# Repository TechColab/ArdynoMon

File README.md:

# ArdynoMon
Arduino shield for DIY dynos, engine monitoring &amp; more.  
Designed for monitoring & logging key aspects of an internal combustion engine for the purpose of R&D for my own Engine Management system. 
Aims to be the natural successor for the "Ardyno" shield https://ardyno.weebly.com/ with more input options & logging.  

Basically, it uses the Arduino's two interrupts to accuately record one or two channels of engine cycle events.  
While the original Ardyno would use one signal from an inertia drum roller & one signal from the ignition system, this ArdynoMon can alternatively be used to get both signals from different parts of the ignition system.  

# 2026-02-14 Revision 3.6 addresses all know issues.
    After some external interest (thank you) I've been nudged into refreshing this page.  
	I still get a bit lost with KiCAD files so if I've missed one from the upload, let me know.  
    Amusingly, I have recently used it to check th timing of a minimal EVSE (EV charger) I've built.  

# 2023-07-31 Don't use this version.
    Significant updated coming shortly to address the following issues with this version:  
	I accepted a subtitution of the transistors without realising that they have a different pinout.  
 	The RX going through the level shifter prevents in-situ programming.  
  	Better to choose the regulator on the Arduino *OR* the one on ArdynoMon shield, but not both!  
   	Both 1-Wire busses need a power pin as passive power is not always wanted.  

## 1.) updates from Ardyno Rev1  
	- drop A4 & A5 reducing on-board analogue inputs from 6 to 4.  
	+ frees I2C to go with UART & SPI  
	+ accept 1-wire digital temperature sensors (both 5V & 3.3V) bus powered or not  
	+ accept trigger from coil primary. Option for lo-V (5-12V COP) or hi-V (400V CDI/IDI)  
	+ accept trigger from 12V (& 5V) Hall effect sensors with suitable protection. Rising or Falling edge    
	+ option for VR conditioner / Opto-isolator plug-in board  
		E.g. in addition to coil primary trigger for measuring dwell time  
	+ gives 2 digital I/Os for PWM, servo, Dir+Step, analogue output etc.
		E.g. PWM eddie current brake & servo throttle  
		E.g. foot-switch to trigger logging time-stamp 'way-point'  
	+ better use of coastline with 3-pin 90-degree pin headers, can also use IDC ribbon cable connectors  
	+ all key signals are 3V & 5V  
	+ replace 555 timing C & R with 1nF (as close as poss) & 1k + optional 2M trim-pot for variable pulse width  
	+ put LED on output of 555 to aid diagnosing pick-ups which use it  
	= wider audience, upgradable, inline with YourDyno  

## 2.) additional monitoring features integrated
	+ uSD/TF on SPI, sharable with other SPI devices
	+ ambient humidity, air pressure, temperature on I2C  
	+ RTC on I2C  
	+ jumper option with resistor divider to measure vehicle battery voltage
	= fully integrated logger (not just ArdynoMon) better than existing one. Can share SPI, doesn't use analogue pins  

## 3.) designed-for optional ad-hoc add-ons
	drive individually addressable RGB LEDs for rev-counter & other indicators etc.
	serial logging via Bluetooth or WiFi module. On pigtails to get out of Faraday cage  
	current sensor on COP to find required dwell time - to one of the analogue inputs  
	RS485 bus for multi-drop peripheral/controller  
	1-wire: DS18b20, K-type thermocouple amplifiers, battery monitor  
	I2C: 24-bit ADC strain-guage amplifier, IMU  
	SPI: CAN bus?
	published (push-pull buffered) sync pulse from conditioned signal. For tacho, etc. (crank & cycle)  
	can drive high power COB LEDs via MOSFET for simple ignition strobe light  

# Uses:

Monitor the ignition trigger pick-up & the coil to capture the advance/retard curve of the CDI/IDI system.  
Monitor the coil primary to capture the dwell time variation of an induction (IDI) system.  
Monitor the RPM & drive an LED ring for rev-counter with MOSFET for rev-limmiter or auto-shift.  
Add supplimental injection system: N2O, H2O etc.

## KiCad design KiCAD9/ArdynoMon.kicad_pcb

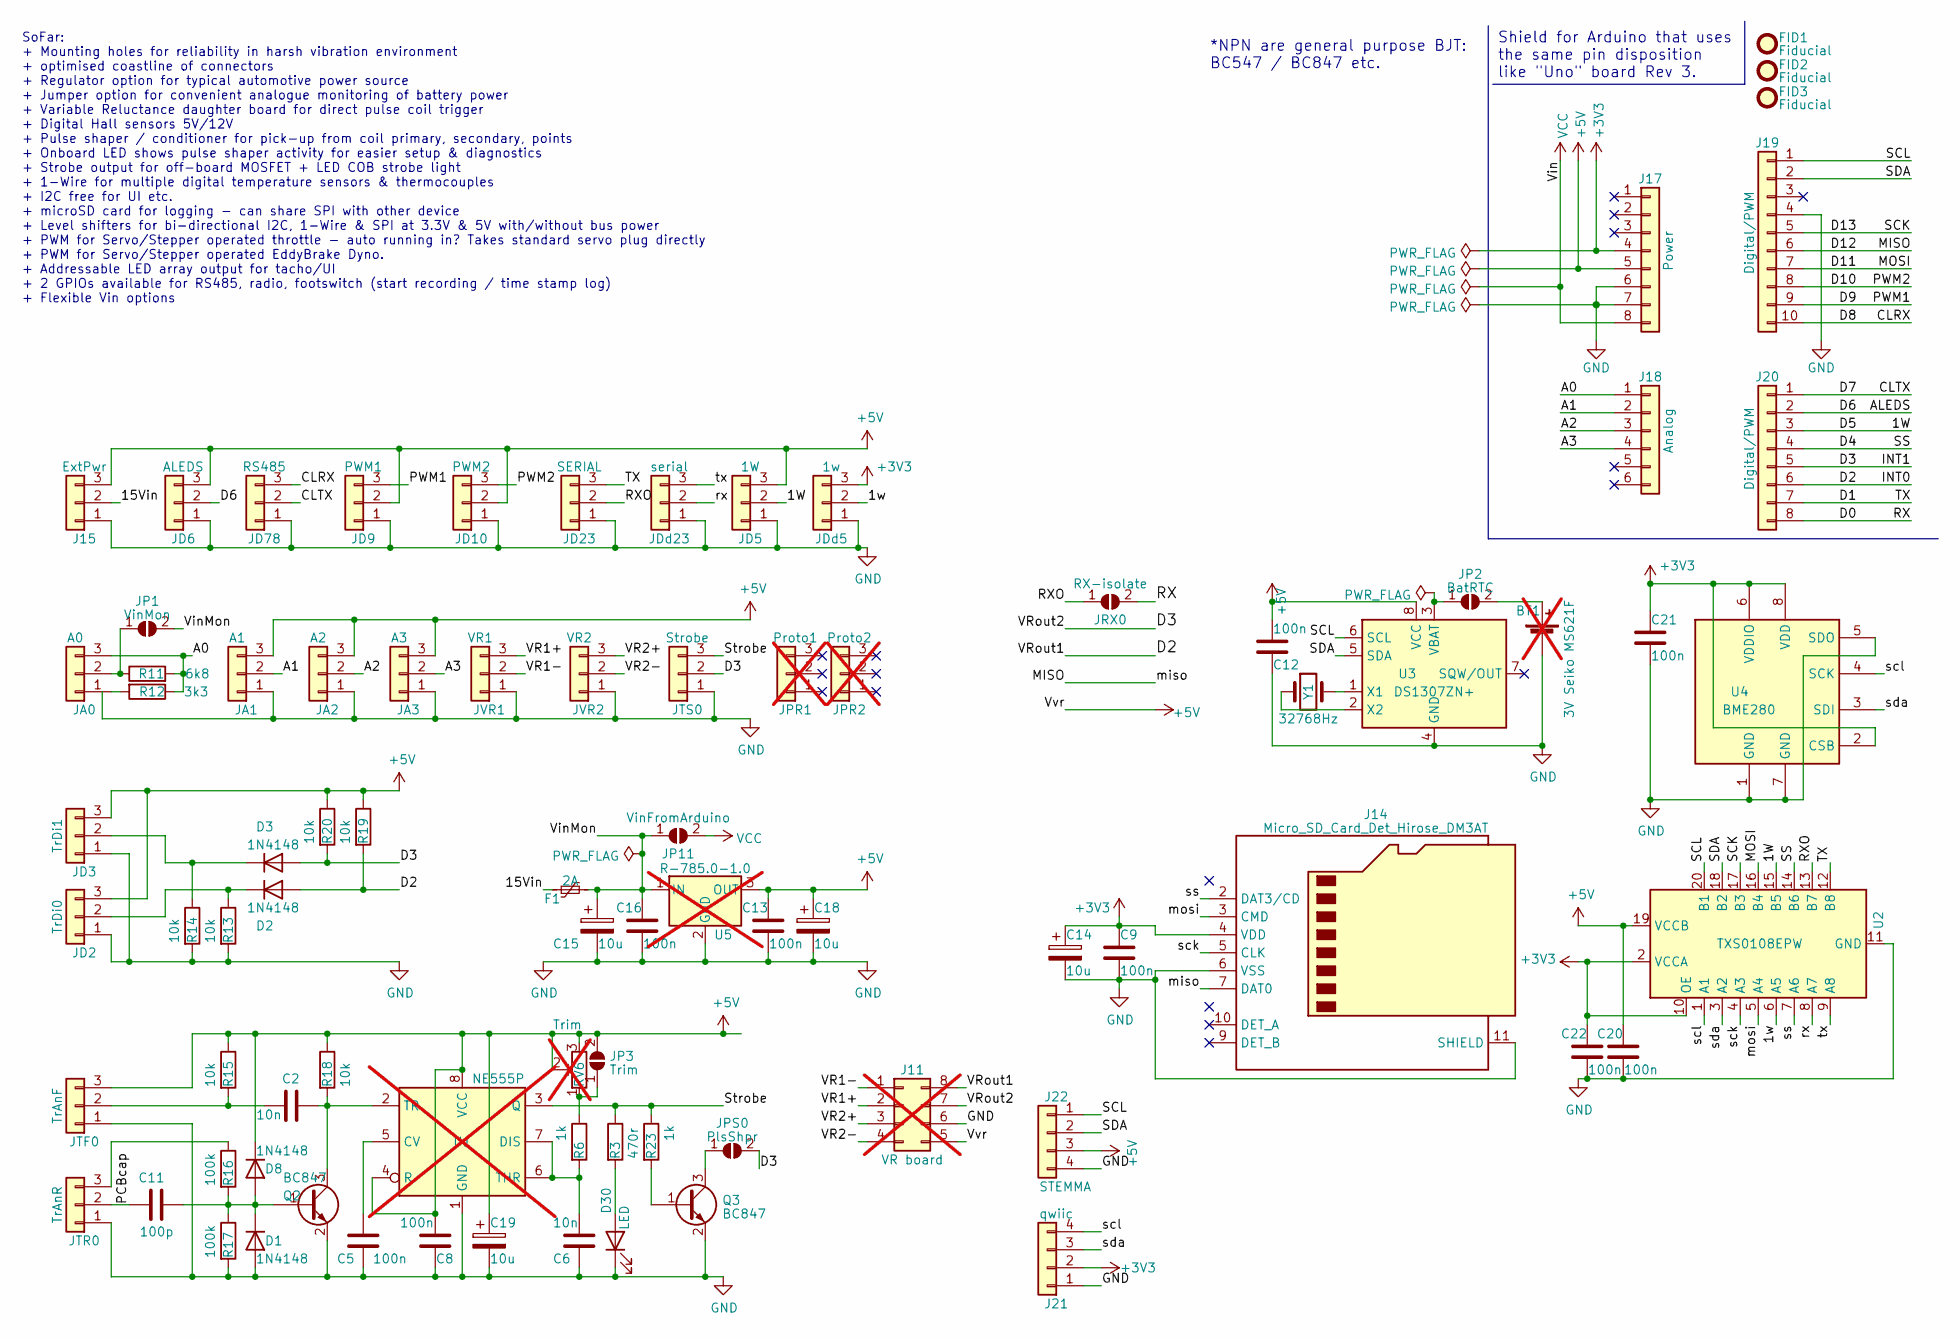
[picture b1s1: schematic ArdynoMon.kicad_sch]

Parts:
BT1: 3V Seiko MS621F; BatteryHolder_Seiko_MS621F; not fitted
C2, C6: 10n; C_0603_1608Metric; MFG Part Num GRM188R71E103KA01D
C5, C8, C9, C12, C13, C16, C20, C21, C22: 100n; C_0603_1608Metric; MFG Part Num 06033G104ZAT4A
C11: 100p; C_0603_1608Metric; MFG Part Num VJ0603Y101MXXCW1BC
C14, C15, C18, C19: 10u; C_0603_1608Metric; MFG Part Num GRM188R61E106MA73J
D1, D2, D3, D8: 1N4148; D_0603_1608Metric; MFG Part Num TS4148C RCG
D30: LED; LED_0805_2012Metric_Pad1.15x1.40mm_HandSolder; MFG Part Num LTST-C191TBKT
F1: 2A; Fuse_0805_2012Metric_Pad1.15x1.40mm_HandSolder; MFG Part Num 0805L200SLTHYR
FID1, FID2, FID3: Fiducial; Fiducial_0.5mm_Mask1mm
J11: VR board; DIP-8_W7.62mm_Socket; not fitted
J14: Micro_SD_Card_Det_Hirose_DM3AT; microSD_HC_Molex_104031-0811; MFG Part Num 104031-0831
J15: ExtPwr; PinHeader_1x03_P2.54mm_Vertical
J17: Power; PinSocket_1x08_P2.54mm_Vertical
J18: Analog; PinSocket_1x06_P2.54mm_Vertical
J19: Digital/PWM; PinSocket_1x10_P2.54mm_Vertical
J20: Digital/PWM; PinSocket_1x08_P2.54mm_Vertical
J21: qwiic; JST_SH_BM04B-SRSS-TB_1x04-1MP_P1.00mm_Vertical; MFG Part Num BM04B-SRSS-TB
J22: STEMMA; JST_PH_B4B-PH-K_1x04_P2.00mm_Vertical; MFG Part Num B4B-PH-K-S (LF)(SN)
JA0: A0; PinHeader_1x03_P2.54mm_Vertical
JA1: A1; PinHeader_1x03_P2.54mm_Vertical
JA2: A2; PinHeader_1x03_P2.54mm_Vertical
JA3: A3; PinHeader_1x03_P2.54mm_Vertical
JD2: TrDi0; PinHeader_1x03_P2.54mm_Vertical
JD3: TrDi1; PinHeader_1x03_P2.54mm_Vertical
JD5: 1W; PinHeader_1x03_P2.54mm_Vertical
JD6: ALEDS; PinHeader_1x03_P2.54mm_Vertical
JD9: PWM1; PinHeader_1x03_P2.54mm_Vertical
JD10: PWM2; PinHeader_1x03_P2.54mm_Vertical
JD23: SERIAL; PinHeader_1x03_P2.54mm_Vertical
JD78: RS485; PinHeader_1x03_P2.54mm_Vertical
JDd5: 1w; PinHeader_1x03_P2.54mm_Vertical
JDd23: serial; PinHeader_1x03_P2.54mm_Vertical
JP1: VinMon; SolderJumper-2_P1.3mm_Open_RoundedPad1.0x1.5mm
JP2: BatRTC; SolderJumper-2_P1.3mm_Open_RoundedPad1.0x1.5mm
JP3: Trim; SolderJumper-2_P1.3mm_Bridged_RoundedPad1.0x1.5mm
JP11: VinFromArduino; SolderJumper-2_P1.3mm_Open_RoundedPad1.0x1.5mm
JPR1: Proto1; PinHeader_1x03_P2.54mm_Vertical; not fitted
JPR2: Proto2; PinHeader_1x03_P2.54mm_Vertical; not fitted
JPS0: PlsShpr; SolderJumper-2_P1.3mm_Bridged_RoundedPad1.0x1.5mm
JRX0: RX-isolate; SolderJumper-2_P1.3mm_Bridged_RoundedPad1.0x1.5mm
JTF0: TrAnF; PinHeader_1x03_P2.54mm_Vertical
JTR0: TrAnR; PinHeader_1x03_P2.54mm_Vertical
JTS0: Strobe; PinHeader_1x03_P2.54mm_Vertical
JVR1: VR1; PinHeader_1x03_P2.54mm_Vertical
JVR2: VR2; PinHeader_1x03_P2.54mm_Vertical
Q2, Q3: BC847; SOT-23; MFG Part Num BC847,215
R3: 470r; R_0603_1608Metric; MFG Part Num ESR03EZPF4700
R6, R23: 1k; R_0603_1608Metric; MFG Part Num ERJ-PA3F1001V
R11: 6k8; R_0603_1608Metric; MFG Part Num ERJPA3F6801V
R12: 3k3; R_0603_1608Metric; MFG Part Num ERJPA3F3301V
R13, R14, R15, R18, R19, R20: 10k; R_0603_1608Metric; MFG Part Num ERJPA3F1002V
R16, R17: 100k; R_0603_1608Metric; MFG Part Num ERJ-PA3F1003V
RV6: Trim; Potentiometer_Vishay_T73XW_Horizontal; not fitted
U1: NE555P; DIP-8_W7.62mm; not fitted
U2: TXS0108EPW; TSSOP-20_4.4x6.5mm_P0.65mm; MFG Part Num TXS0108EPW
U3: DS1307ZN+; SOIC-8_3.9x4.9mm_P1.27mm; MFG Part Num DS1307ZN+T&R
U4: BME280; Bosch_LGA-8_2.5x2.5mm_P0.65mm_ClockwisePinNumbering; MFG Part Num BME280
U5: R-785.0-1.0; Converter_DCDC_RECOM_R-78E-0.5_THT; not fitted
Y1: 32768Hz; Crystal_SMD_2012-2Pin_2.0x1.2mm_HandSoldering; MFG Part Num RT2012-32.768-6-TR

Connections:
+3V3: C9.1, C14.1, C21.1, C22.1, J14.4 (VDD), J17.4, J21.2, JDd5.3, U2.2 (VCCA), U2.10 (OE), U4.2 (CSB), U4.6 (VDDIO), U4.8 (VDD)
+5V: C8.1, C12.1, C13.1, C18.1, C19.1, C20.1, D8.1 (K), J11.5, J15.3, J17.5, J22.3, JA1.3, JA2.3, JA3.3, JD2.3, JD3.3, JD5.3, JD6.3, JD9.2, JD10.2, JP3.2 (B), JTF0.3, R15.1, R18.1, R19.1, R20.1, RV6.2, RV6.3, U1.4 (R), U1.8 (VCC), U2.19 (VCCB), U3.8 (VCC), U5.3 (OUT)
/1W: J20.3, JD5.2, U2.15 (B5)
/1w: JDd5.2, U2.6 (A5)
/15Vin: F1.1, J15.2
/A0: J18.1, JA0.3, R11.2, R12.1
/A1: J18.2, JA1.2
/A2: J18.3, JA2.2
/A3: J18.4, JA3.2
/ALEDS: J20.2, JD6.2
/CLRX: J19.10, JD78.3
/CLTX: J20.1, JD78.2
/D0: J20.8, JRX0.2 (B)
/D1: J20.7, JD23.3, U2.12 (B8)
/D2: D2.2 (A), J11.8, J20.6, R19.2
/D3: D3.2 (A), J11.7, J20.5, JPS0.2 (B), JTS0.2, R20.2
/D4: J20.4, U2.14 (B6)
/D9: J19.9, JD9.3
/D10: J19.8, JD10.3
/D11: J19.7, U2.16 (B4)
/D12: J14.7 (DAT0), J19.6
/D13: J19.5, U2.17 (B3)
/PCBcap: C11.1, JTR0.2
/RXO: JD23.2, JRX0.1 (A), U2.13 (B7)
/SCL: J19.1, J22.1, U2.20 (B1), U3.6 (SCL)
/SDA: J19.2, J22.2, U2.18 (B2), U3.5 (SDA)
/Strobe: JTS0.3, R3.1, R23.1, U1.3 (Q)
/VR1+: J11.2, JVR1.3
/VR1-: J11.1, JVR1.2
/VR2+: J11.3, JVR2.3
/VR2-: J11.4, JVR2.2
/VinMon: C15.1, C16.1, F1.2, JP1.2 (B), JP11.1 (A), U5.1 (IN)
/mosi: J14.3 (CMD), U2.5 (A4)
/rx: JDd23.2, U2.8 (A7)
/sck: J14.5 (CLK), U2.4 (A3)
/scl: J21.4, U2.1 (A1), U4.4 (SCK)
/sda: J21.3, U2.3 (A2), U4.3 (SDI)
/ss: J14.2 (DAT3/CD), U2.7 (A6)
/tx: JDd23.3, U2.9 (A8)
GND: BT1.2 (-), C5.2, C6.2, C8.2, C9.2, C12.2, C13.2, C14.2, C15.2, C16.2, C18.2, C19.2, C20.2, C21.2, C22.2, D1.2 (A), D30.1 (K), J11.6, J14.6 (VSS), J14.11 (SHIELD), J15.1, J17.6, J17.7, J19.4, J21.1, J22.4, JA1.1, JA2.1, JA3.1, JD2.1, JD3.1, JD5.1, JD6.1, JD9.1, JD10.1, JD23.1, JD78.1, JDd5.1, JDd23.1, JTF0.1, JTR0.1, JTS0.1, JVR1.1, JVR2.1, Q2.2 (E), Q3.2 (E), R13.2, R14.2, R17.2, U1.1 (GND), U2.11 (GND), U3.4 (GND), U4.1 (GND), U4.5 (SDO), U4.7 (GND), U5.2 (GND)
unnamed: JP2.1 (A), U3.3 (VBAT)
unnamed: BT1.1 (+), JP2.2 (B)
unnamed: C11.2, D1.1 (K), D8.2 (A), Q2.1 (B), R16.2, R17.1
unnamed: D2.1 (K), JD2.2, R13.1
unnamed: D3.1 (K), JD3.2, R14.1
unnamed: D30.2 (A), R3.2
unnamed: JA0.1, R12.2
unnamed: JA0.2, JP1.1 (A), R11.1
unnamed: JP3.1 (A), R6.1, RV6.1
unnamed: JPS0.1 (A), Q3.3 (C)
unnamed: C2.1, JTF0.2, R15.2
unnamed: JTR0.3, R16.1
unnamed: C2.2, Q2.3 (C), R18.2, U1.2 (TR)
unnamed: Q3.1 (B), R23.2
unnamed: C5.1, U1.5 (CV)
unnamed: C6.1, R6.2, U1.6 (THR), U1.7 (DIS)
unnamed: U3.1 (X1), Y1.2
unnamed: U3.2 (X2), Y1.1
VCC: J17.8, JP11.2 (B)

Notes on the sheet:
*NPN are general purpose BJT: BC547 / BC847 etc.
Shield for Arduino that uses the same pin disposition like "Uno" board Rev 3.
SoFar: + Mounting holes for reliability in harsh vibration environment + optimised coastline of connectors + Regulator option for typical automotive power source + Jumper option for convenient analogue monitoring of battery power + Variable Reluctance daughter board for direct pulse coil trigger + 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

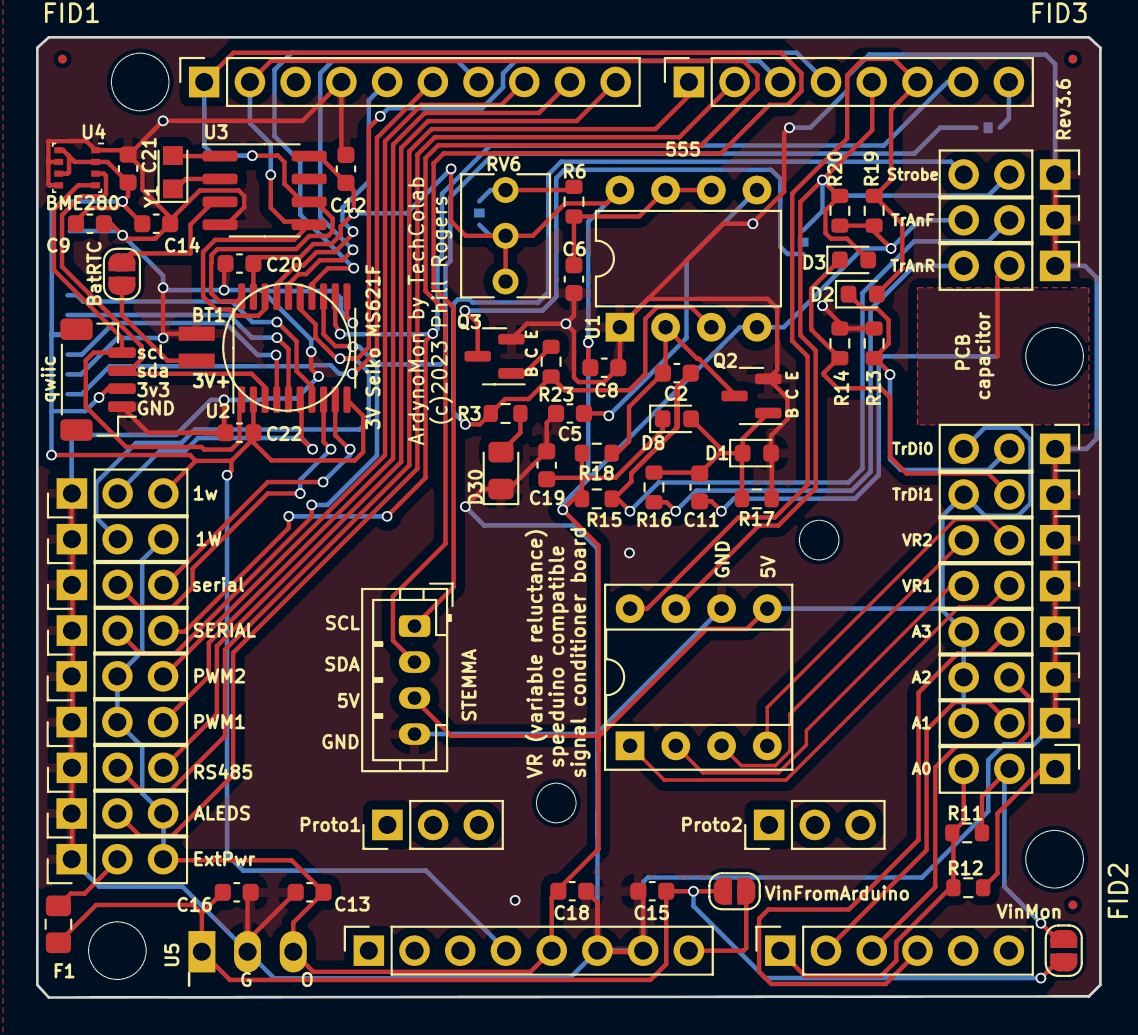
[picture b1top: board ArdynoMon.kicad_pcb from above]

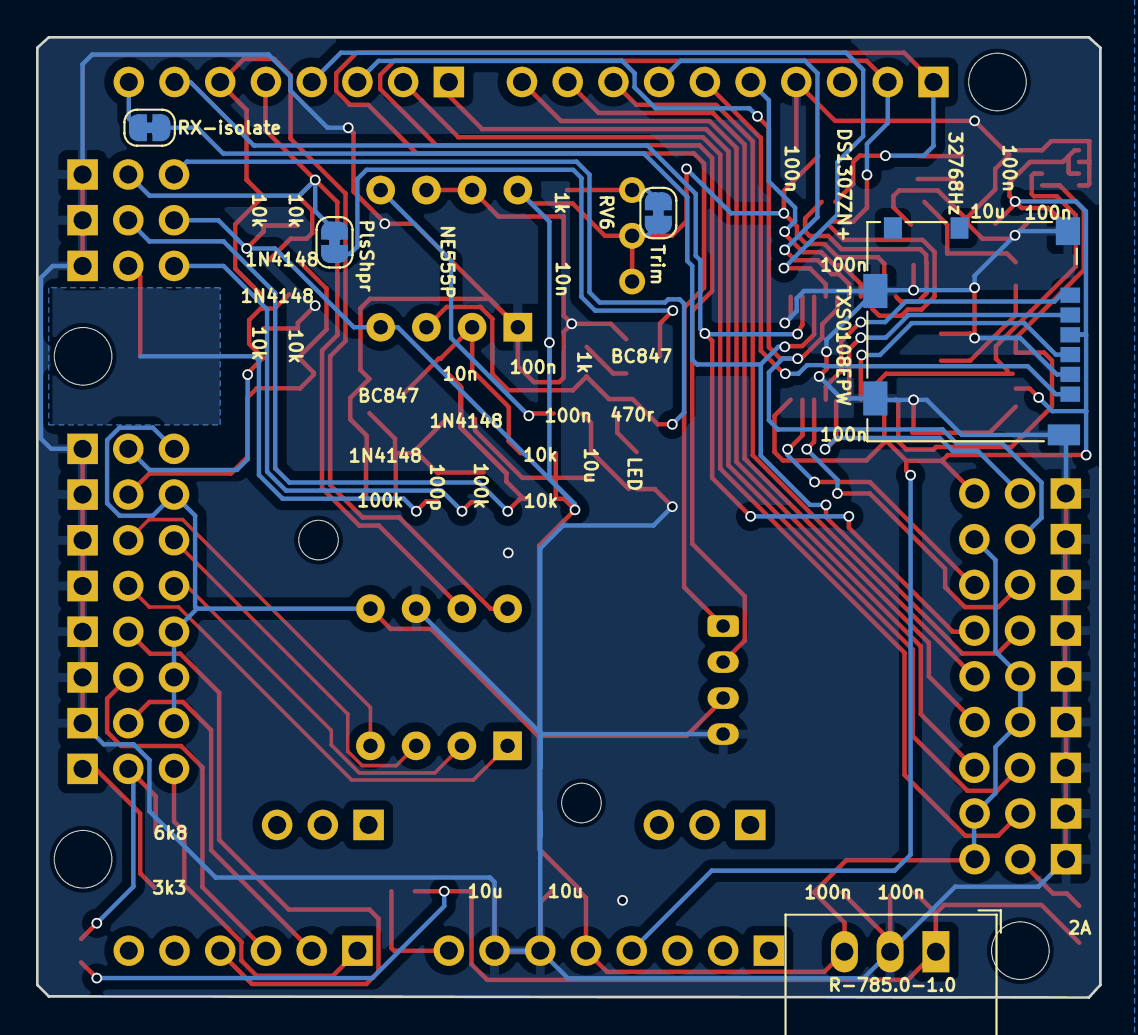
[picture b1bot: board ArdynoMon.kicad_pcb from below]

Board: 2 copper layers, 59.1 x 53.3 mm, 88 parts (5 on the bottom side), 59 nets.

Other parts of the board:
MH1, MH2, MH3, MH4: MountingHole_3.2mm

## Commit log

2023-07-01 Pics
2023-07-31 Wait for r3.6
2026-02-14 Rev. 3.6
2026-02-14 Rev 3.6
2026-02-14 Photo of prototype with mods and 3-row 90-degree pin connectors

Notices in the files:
KiCAD9/ArdynoMon.kicad_pcb:
(c)2023 Phill Rogers
